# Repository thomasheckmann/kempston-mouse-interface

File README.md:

# kempston-mouse-interface
Kempston mouse interface for ZX Spectrum

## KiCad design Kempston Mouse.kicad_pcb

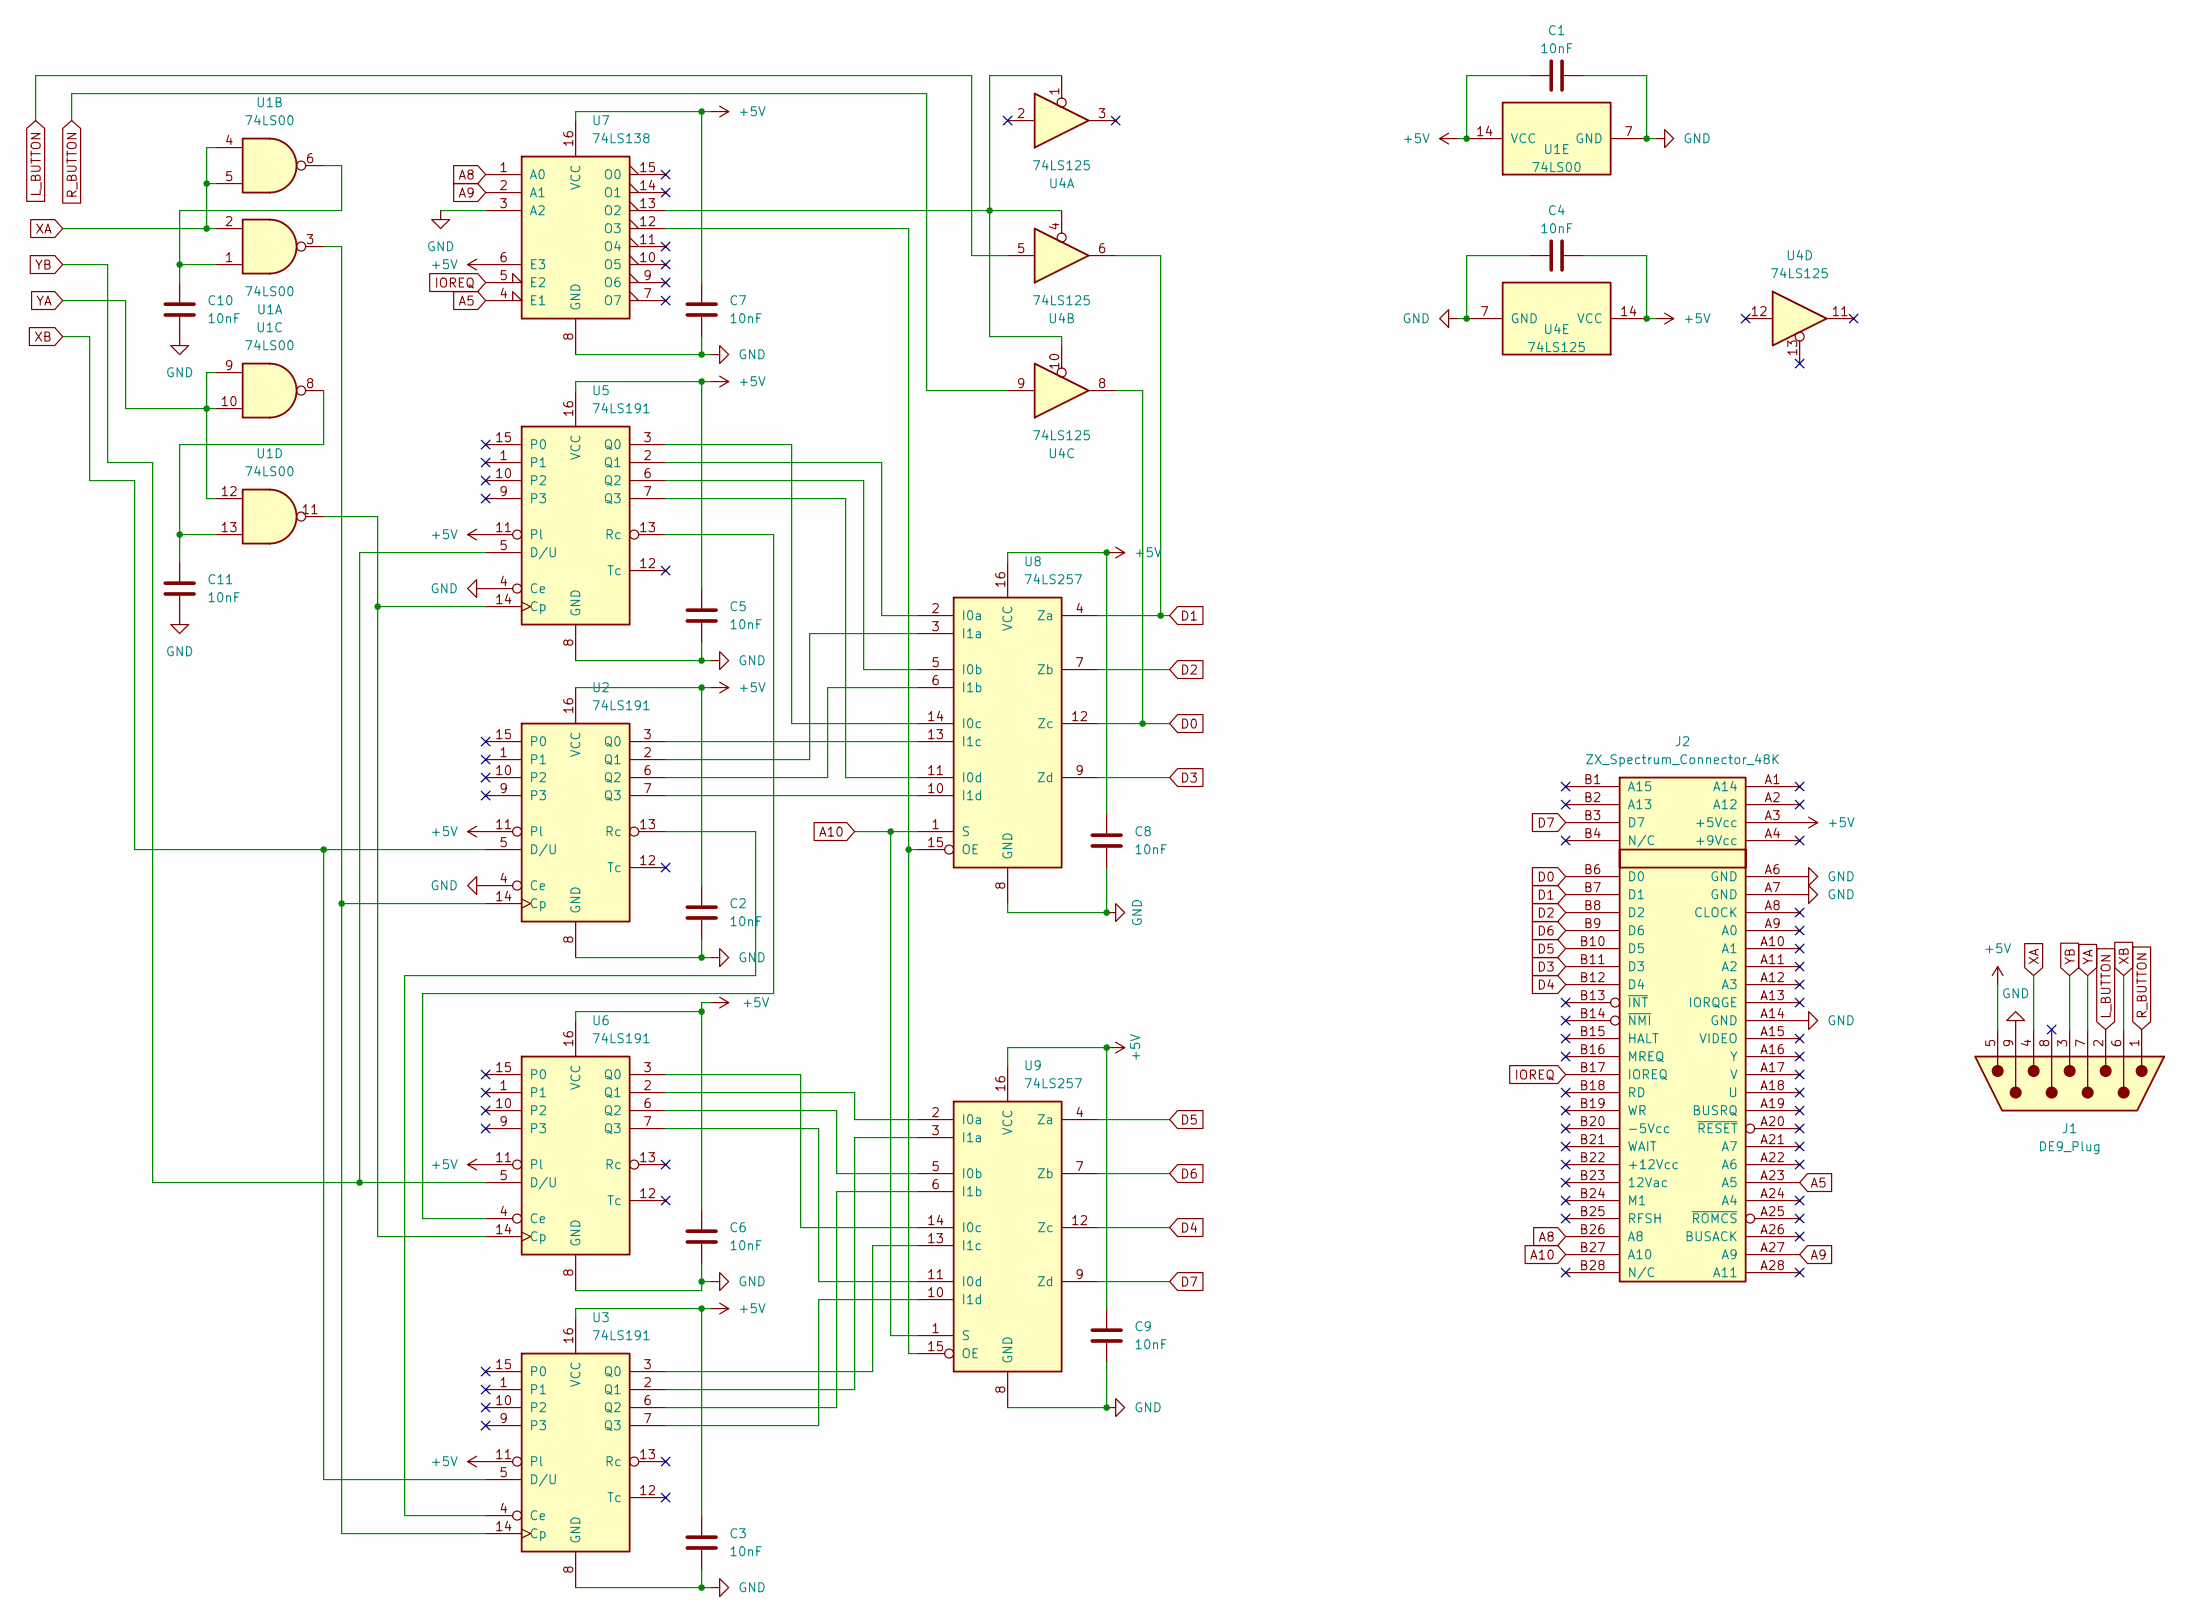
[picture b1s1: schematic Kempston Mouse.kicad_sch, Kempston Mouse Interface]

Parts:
C1, C2, C3, C4, C5, C6, C7, C8, C9, C10, C11: 10nF; C_Disc_D3.0mm_W1.6mm_P2.50mm
J1: DE9_Plug; DSUB-9_Male_Horizontal_P2.77x2.84mm_EdgePinOffset4.94mm_Hou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
J2: ZX_Spectrum_Connector_48K; ZX_EDGE
U1: 74LS00; DIP-14_W7.62mm
U2, U3, U5, U6: 74LS191; DIP-16_W7.62mm
U4: 74LS125; DIP-14_W7.62mm
U7: 74LS138; DIP-16_W7.62mm
U8, U9: 74LS257; DIP-16_W7.62mm

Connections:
+5V: C1.1, C2.1, C3.1, C4.2, C5.1, C6.1, C7.1, C8.1, C9.1, J1.5, J2.A3 (+5Vcc), U1.14 (VCC), U2.11 (Pl), U2.16 (VCC), U3.11 (Pl), U3.16 (VCC), U4.14 (VCC), U5.11 (Pl), U5.16 (VCC), U6.11 (Pl), U6.16 (VCC), U7.6 (E3), U7.16 (VCC), U8.16 (VCC), U9.16 (VCC)
A5: J2.A23 (A5), U7.4 (E1)
A8: J2.B26 (A8), U7.1 (A0)
A9: J2.A27 (A9), U7.2 (A1)
A10: J2.B27 (A10), U8.1 (S), U9.1 (S)
D0: J2.B6 (D0), U4.8, U8.12 (Zc)
D1: J2.B7 (D1), U4.6, U8.4 (Za)
D2: J2.B8 (D2), U8.7 (Zb)
D3: J2.B11 (D3), U8.9 (Zd)
D4: J2.B12 (D4), U9.12 (Zc)
D5: J2.B10 (D5), U9.4 (Za)
D6: J2.B9 (D6), U9.7 (Zb)
D7: J2.B3 (D7), U9.9 (Zd)
GND: C1.2, C2.2, C3.2, C4.1, C5.2, C6.2, C7.2, C8.2, C9.2, C10.2, C11.2, J1.9, J2.A6 (GND), J2.A7 (GND), J2.A14 (GND), U1.7 (GND), U2.4 (Ce), U2.8 (GND), U3.8 (GND), U4.7 (GND), U5.4 (Ce), U5.8 (GND), U6.8 (GND), U7.3 (A2), U7.8 (GND), U8.8 (GND), U9.8 (GND)
IOREQ: J2.B17 (IOREQ), U7.5 (E2)
L_BUTTON: J1.2, U4.5
unnamed: C10.1, U1.1, U1.6
unnamed: C11.1, U1.8, U1.13
unnamed: U1.3, U2.14 (Cp), U3.14 (Cp)
unnamed: U2.3 (Q0), U8.13 (I1c)
unnamed: U2.2 (Q1), U8.3 (I1a)
unnamed: U2.6 (Q2), U8.6 (I1b)
unnamed: U2.7 (Q3), U8.10 (I1d)
unnamed: U2.13 (Rc), U3.4 (Ce)
unnamed: U3.3 (Q0), U9.13 (I1c)
unnamed: U3.2 (Q1), U9.3 (I1a)
unnamed: U3.6 (Q2), U9.6 (I1b)
unnamed: U3.7 (Q3), U9.10 (I1d)
unnamed: U1.11, U5.14 (Cp), U6.14 (Cp)
unnamed: U5.3 (Q0), U8.14 (I0c)
unnamed: U5.2 (Q1), U8.2 (I0a)
unnamed: U5.6 (Q2), U8.5 (I0b)
unnamed: U5.7 (Q3), U8.11 (I0d)
unnamed: U5.13 (Rc), U6.4 (Ce)
unnamed: U6.3 (Q0), U9.14 (I0c)
unnamed: U6.2 (Q1), U9.2 (I0a)
unnamed: U6.6 (Q2), U9.5 (I0b)
unnamed: U6.7 (Q3), U9.11 (I0d)
unnamed: U4.1, U4.4, U4.10, U7.13 (O2)
unnamed: U7.12 (O3), U8.15 (OE), U9.15 (OE)
R_BUTTON: J1.1, U4.9
XA: J1.4, U1.2, U1.4, U1.5
XB: J1.6, U2.5 (D/U), U3.5 (D/U)
YA: J1.7, U1.9, U1.10, U1.12
YB: J1.3, U5.5 (D/U), U6.5 (D/U)

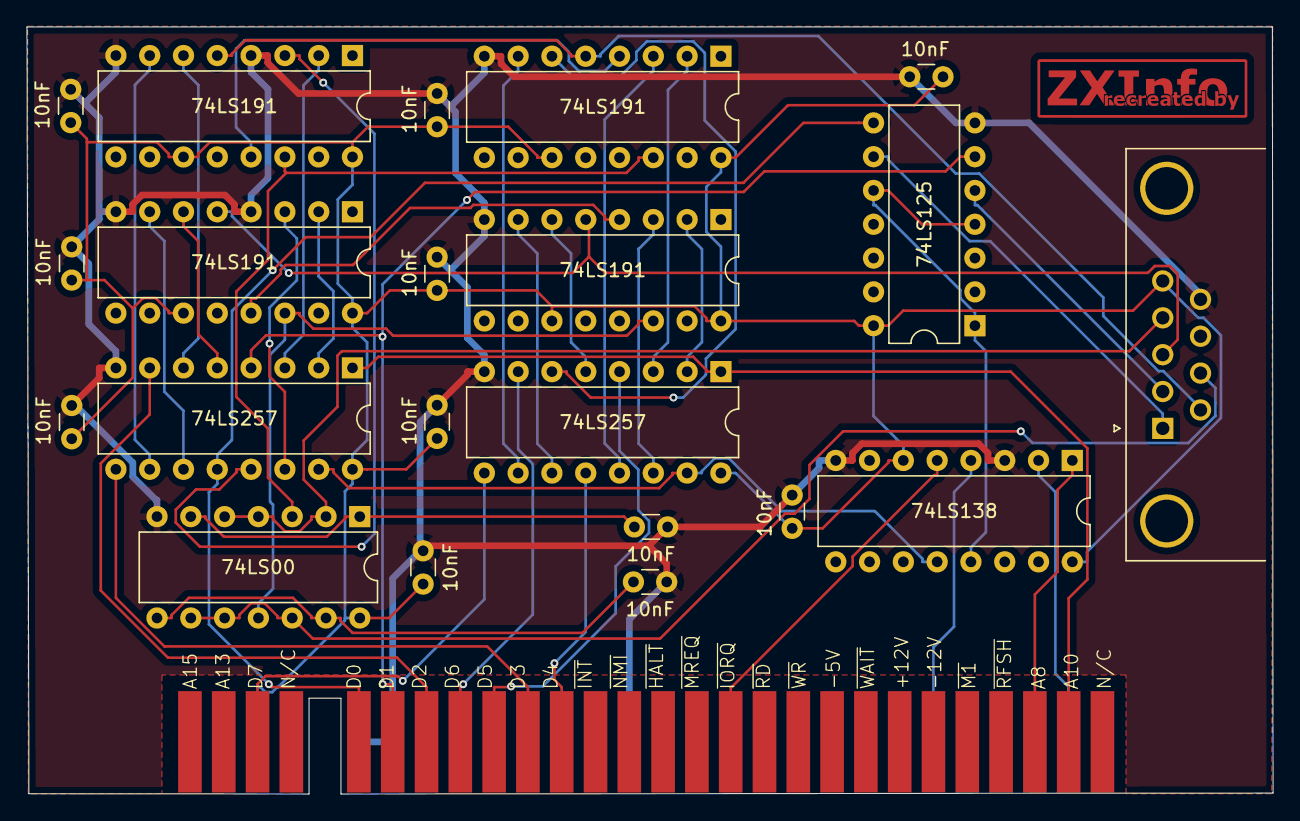
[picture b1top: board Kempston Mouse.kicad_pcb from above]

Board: 2 copper layers, 93.7 x 57.6 mm, 23 parts (0 on the bottom side), 45 nets.

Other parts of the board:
G200: LOGO; ZXInfo_kicad_logo_copper_16.5x5

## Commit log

2024-03-08 Added tracks to PCB
2024-03-08 Layout to fit into BUS Extender
